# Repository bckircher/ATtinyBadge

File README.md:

Copyright &copy; 2026 Brian Kircher

Open Source Software: you can modify and/or share it under the terms of the BSD
license file in the root directory of this project.

# ATtinyBadge

This project is a small (75.2 mm by 44.7 mm) circuit board in the shape of the
FIRST&reg; logo.  Each symbol in the logo is painted the appropriate color, and
has a set of 11 LEDs (of matching color).  It is powered by a single CR2032
coin cell battery, which provides a typical run time of 24 hours.

Once turned on, a random, short animation is played once a minute.  Once in a
while, a special, longer animation is played instead.  Pressing the button
causes another animation to be played without further delay (canceling the one
minute delay).  Holding the button for two seconds turns the badge off, placing
it into an extremely low power mode.  This also happens after the badge has
been running for eight hours (so it doesn't run continously until the battery
is fully depleted).  When off, pressing the button turns it back on and repeats
the process.

Full details of the design, development, and construction process can be found
[here](https://bckircher.github.io/ATtinyBadge).

## Hardware

The board is designed using [KiCad](https://www.kicad.org/), with the design
files and resulting gerbers provided in the `hardware` directory.  It uses 6/6
design rules, with a 12 mil minimum drill size, so it should be easily
manufactured by any number of prototype board shops (so long as they are able
to make the very odd, non-rectangular shape of the board).  My personal
preference is [PCBWay](https://www.pcbway.com/).

The components are populated by hand (since the board has components on both
sides, the hot plate technique only works for one side!), and the PCB is then
hand painted to match the FIRST logo and protected with a coating of a spray
sealer.  Safety pins like
[these](https://www.amazon.com/Locking-Safety-Brooch-Silver-Jewelry/dp/B0DNQFC7CN)
are soldered to the exposed pad at the top of the back and used to attach the
badge to a shirt/lapel/etc.

## Firmware

The firmware that runs on the ATtiny1616 is written using
[TinyGo](https://tinygo.org), and is provided in the `firmware` directory.
One space saving optimization that could be done is a custom target that does
not enable the timing services that are a standard part of the TinyGo targets;
that timer is simply disabled after the application starts, making all the
timer setup code effectively "dead code" (even though it still exists and
runs).

The firmware can also be built and run natively (using normal Go) in order to
develop, debug, and test new animations.  It uses ANSI control sequences with
the command line terminal to generate an ASCII-art simulation of the LED array,
with the LEDs "lighting up" as defined by the animation (with the same timing).

## Trademarks

FIRST&reg; is a trademark of For Inspiration and Recognition of Science and
Technology (FIRST), which does not sponsor, authorize, or endorse this project.

It is very much hoped that this does not ruffle any feathers at FIRST,
especially since the color palette could not be _exactly_ adhered to with
off-the-shelf acrylic paints.

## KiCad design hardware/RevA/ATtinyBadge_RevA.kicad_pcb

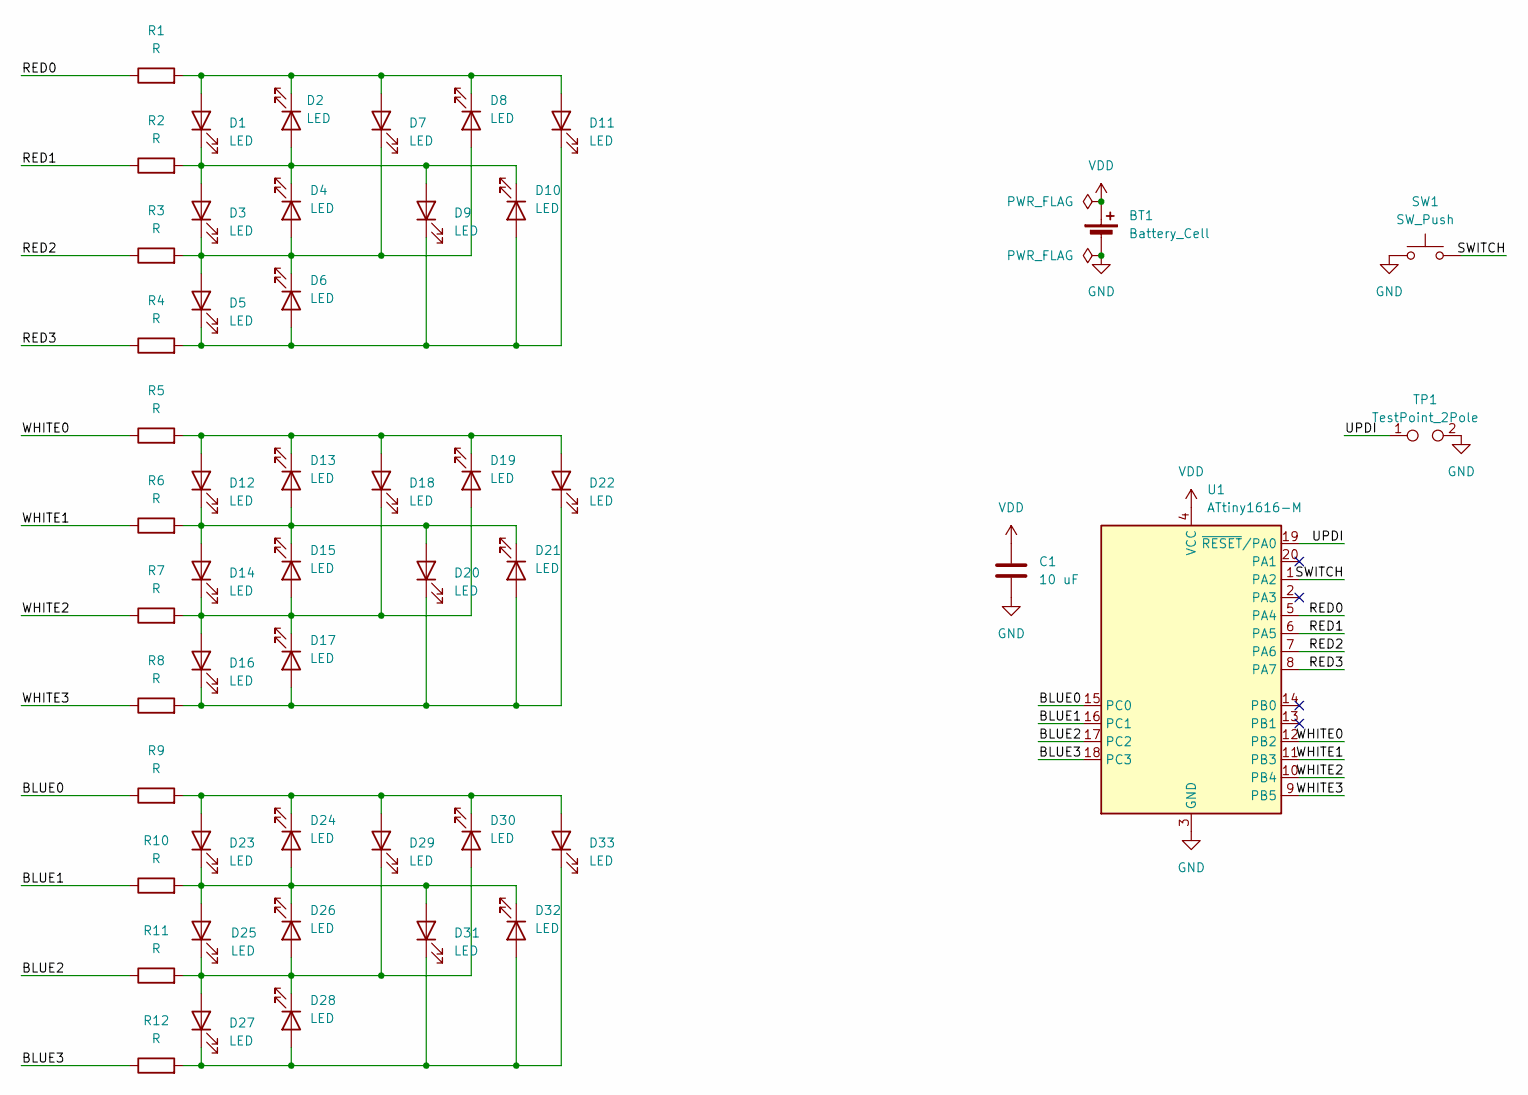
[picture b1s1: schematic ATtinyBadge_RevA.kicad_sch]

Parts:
BT1: Battery_Cell; BatteryHolder_Keystone_1058_1x2032
C1: 10 uF; C_0402_1005Metric_Pad0.74x0.62mm_HandSolder
D1, D2, D3, D4, D5, D6, D7, D8, D9, D10, D11, D12, D13, D14, D15, D16, D17, D18, D19, D20, D21, D22, D23, D24, D25, D26, D27, D28, D29, D30, D31, D32, D33: LED; LED_0402_1005Metric_Pad0.77x0.64mm_HandSolder
R1, R2, R3, R4, R5, R6, R7, R8, R9, R10, R11, R12: R; R_0402_1005Metric_Pad0.72x0.64mm_HandSolder
SW1: SW_Push; SWT0005; PartNo SWT0005-015516SSA
TP1: TestPoint_2Pole; R_2512_6332Metric_Pad1.40x3.35mm_HandSolder
U1: ATtiny1616-M; VQFN-20-1EP_3x3mm_P0.4mm_EP1.7x1.7mm

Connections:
/BLUE0: R9.1, U1.15 (PC0)
/BLUE1: R10.1, U1.16 (PC1)
/BLUE2: R11.1, U1.17 (PC2)
/BLUE3: R12.1, U1.18 (PC3)
/RED0: R1.1, U1.5 (PA4)
/RED1: R2.1, U1.6 (PA5)
/RED2: R3.1, U1.7 (PA6)
/RED3: R4.1, U1.8 (PA7)
/SWITCH: SW1.2, U1.1 (PA2)
/UPDI: TP1.1, U1.19 (~RESET/PA0)
/WHITE0: R5.1, U1.12 (PB2)
/WHITE1: R6.1, U1.11 (PB3)
/WHITE2: R7.1, U1.10 (PB4)
/WHITE3: R8.1, U1.9 (PB5)
GND: BT1.2 (-), C1.2, SW1.1, TP1.2, U1.3 (GND), U1.21 (GND)
unnamed: D1.2 (A), D2.1 (K), D7.2 (A), D8.1 (K), D11.2 (A), R1.2
unnamed: D1.1 (K), D2.2 (A), D3.2 (A), D4.1 (K), D9.2 (A), D10.1 (K), R2.2
unnamed: D3.1 (K), D4.2 (A), D5.2 (A), D6.1 (K), D7.1 (K), D8.2 (A), R3.2
unnamed: D5.1 (K), D6.2 (A), D9.1 (K), D10.2 (A), D11.1 (K), R4.2
unnamed: D12.2 (A), D13.1 (K), D18.2 (A), D19.1 (K), D22.2 (A), R5.2
unnamed: D12.1 (K), D13.2 (A), D14.2 (A), D15.1 (K), D20.2 (A), D21.1 (K), R6.2
unnamed: D14.1 (K), D15.2 (A), D16.2 (A), D17.1 (K), D18.1 (K), D19.2 (A), R7.2
unnamed: D16.1 (K), D17.2 (A), D20.1 (K), D21.2 (A), D22.1 (K), R8.2
unnamed: D23.2 (A), D24.1 (K), D29.2 (A), D30.1 (K), D33.2 (A), R9.2
unnamed: D23.1 (K), D24.2 (A), D25.2 (A), D26.1 (K), D31.2 (A), D32.1 (K), R10.2
unnamed: D25.1 (K), D26.2 (A), D27.2 (A), D28.1 (K), D29.1 (K), D30.2 (A), R11.2
unnamed: D27.1 (K), D28.2 (A), D31.1 (K), D32.2 (A), D33.1 (K), R12.2
VDD: BT1.1 (+), C1.1, U1.4 (VCC)

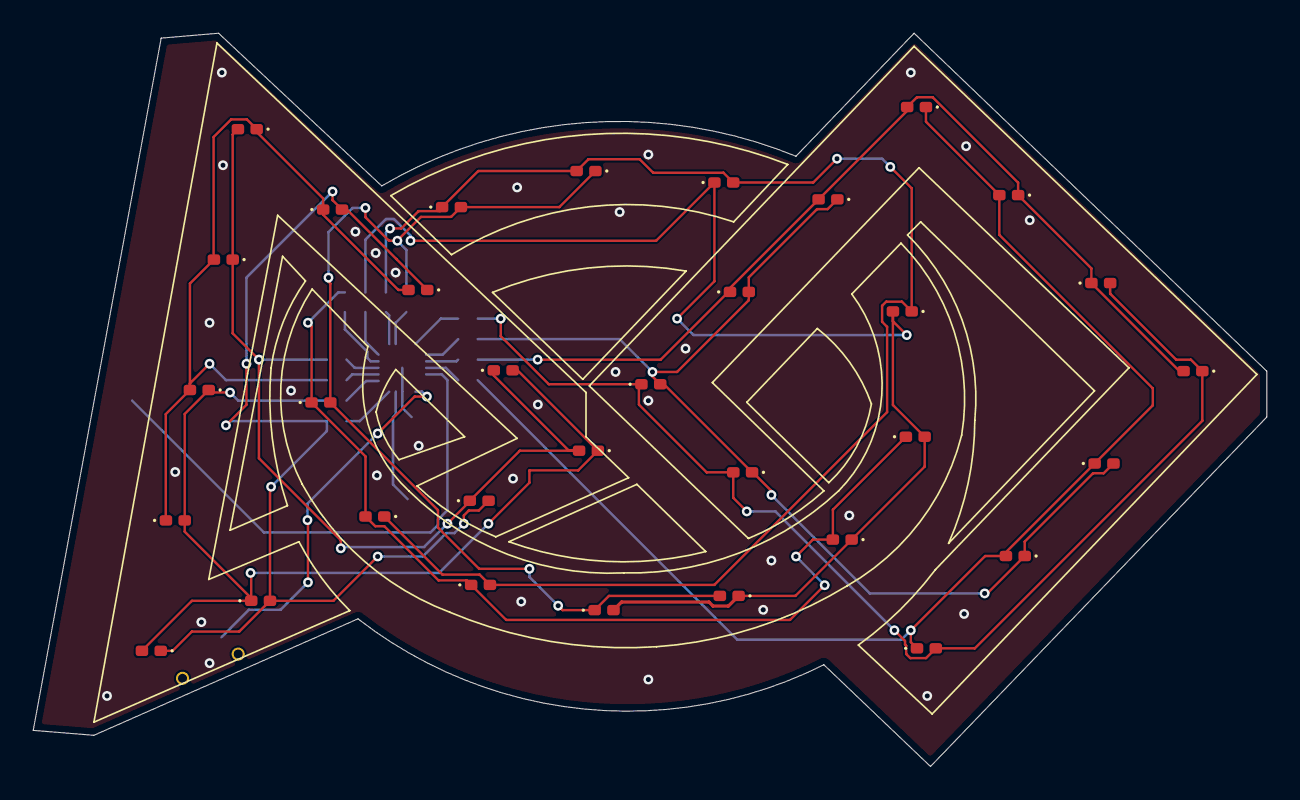
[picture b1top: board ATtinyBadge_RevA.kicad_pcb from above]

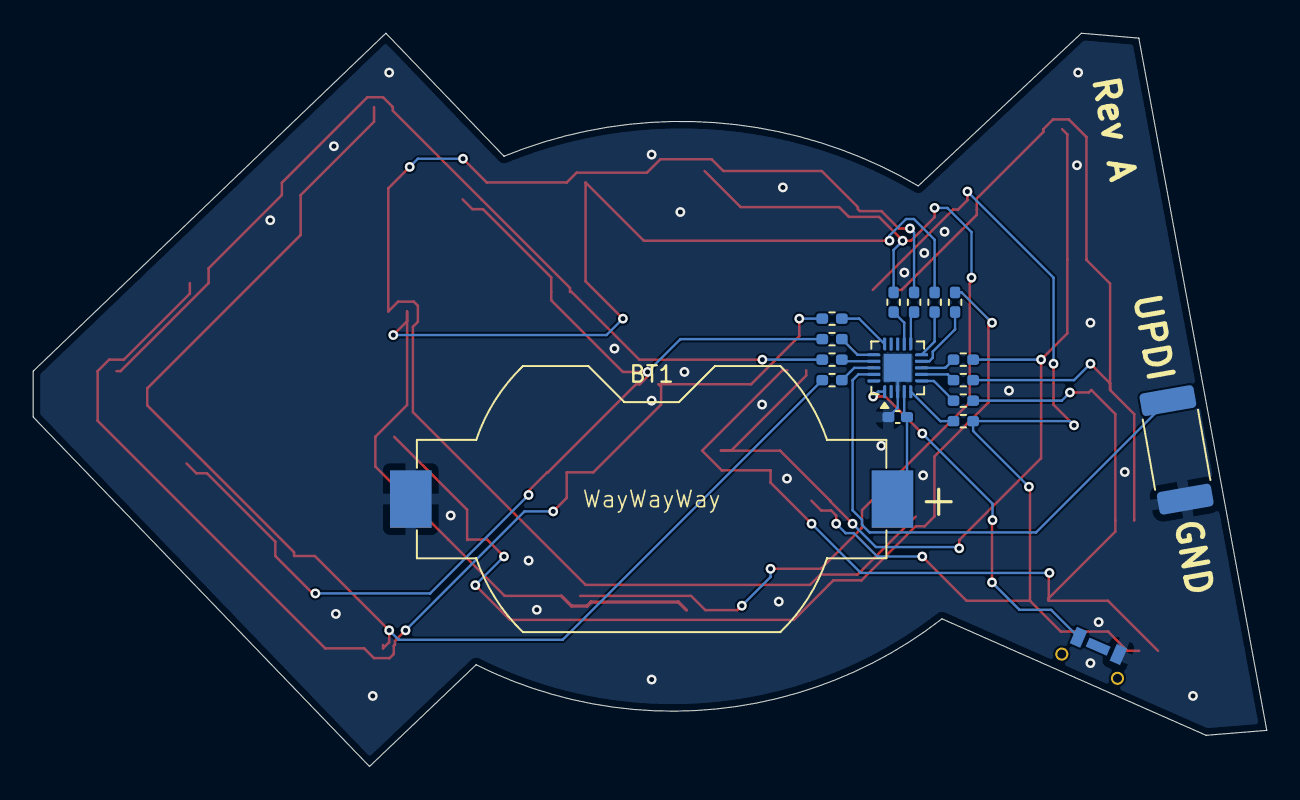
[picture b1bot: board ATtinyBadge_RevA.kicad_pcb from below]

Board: 2 copper layers, 75.2 x 44.7 mm, 50 parts (17 on the bottom side), 28 nets.
